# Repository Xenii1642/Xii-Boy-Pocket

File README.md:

<picture> <source media="(prefers-color-scheme: dark)" srcset="Images/XBP-Logo-Light.png" width="800">  </picture> 

The Xii-Boy Pocket is a small portable Wii using a Game Boy form factor. The Xii-Boy Pocket is the second version of my Xii-Boy design.
This new portable Wii is now better, thinner, and above all, Open-Source ! Compared to the Gboy Rev III, it is 25% smaller and 5mm thinner !

If you want to learn more about it, you can check this BitBuilt Thread: [Xii-Boy Pocket's Thread](https://bitbuilt.net/forums/index.php?threads/the-xii-boy-pocket-v2.6638/)

If you want to see its development, you can check this BitBuilt Worklog: [Xii-Boy Pocket's Worklog](https://bitbuilt.net/forums/index.php?threads/xii-boy-v2-xeniis-second-portable-wii.6374/)

You can also learn more about the Xii-Boy Original here: [Xii-Boy Original Thread](https://bitbuilt.net/forums/index.php?threads/the-xii-boy-xeniis-first-portable-wii.6327/)

If you have any questions or problems about the Xii-Boy Pocket, please let me know 😉 Enjoy !

# Parts
All the parts you need to assemble a Xii-Boy Pocket are listed in the [Xii-Boy V2 Parts List.pdf](https://github.com/Xenii1642/Xii-Boy-Pocket/blob/main/Xii-Boy%20V2%20Parts%20List.pdf) file.

⚠ NOTE ⚠ For the batteries, I personally order mine through [Akkuteile](https://akkuteile.de/). However, if you don't live in Europe, you should buy your batteries somewhere else.
You just have to order two 18650 batteries. You shouldn't order them through Aliexpress, they could be fake and maybe dangerous

# PCB
All the Gerbers you need for the Xii-Boy Pocket are available in the [Gerber](https://github.com/Xenii1642/Xii-Boy-Pocket/tree/main/PCB%20Files/Gerber) folder.

All the needed components are listed in the [Xii-Boy V2 PCB BOM.pdf](https://github.com/Xenii1642/Xii-Boy-Pocket/blob/main/Xii-Boy%20V2%20PCB%20BOM.pdf) file.

The Xii-Boy Pocket's PCBs need specific settings to work properly:

### **Controller PCB**:
- ENIG surface finish 
  
### **Xii-Flex**:
- 0.12mm thickness
- Stiffener Polyimide 0.2 mm
  
### **Main PCB**:
- Impedance Controll YES
- Impedance Controll profile JLC04161H-7628

The other PCBs don't need specific settings. You can just let the setting by default 👍

I personally ordered mine through [JLCPCB](https://jlcpcb.com/) 👍

# Case
All the needed STLs are available in the [STL](https://github.com/Xenii1642/Xii-Boy-Pocket/tree/main/STL) folder.
If you want to order your case in **nylon** or **resin** through [JLC3DP](https://jlc3dp.com/), please use the case available in the [Case (JLC)](https://github.com/Xenii1642/Xii-Boy-Pocket/tree/main/STL/Case%20(JLC)) folder.

Otherwise, if you want to print / order it in FDM, use the case available in the [Case (FDM)](https://github.com/Xenii1642/Xii-Boy-Pocket/tree/main/STL/Case%20(FDM)) folder.

⚠️ Some of the buttons and fixations are too small to be manufactured by JLC3DP. To fix that, you can find a file which contains all the too small pieces [here](https://github.com/Xenii1642/Xii-Boy-Pocket/blob/main/STL/Buttons/Buttons-JLC.stl) ⚠️

I personally ordered my case through [JLC3DP](https://jlc3dp.com/) in **nylon SLS** and I printed the buttons in PLA 👍

⚠ NOTE ⚠ JLC3DP may ask you that there are some risks that the case could have warping or cracks. You have to accept them 👍

# STEP Files
You would like to make an edit on the case? No worries! You can find STEP files of the case in the [STEP folder](https://github.com/Xenii1642/Xii-Boy-Pocket/tree/main/STEP)

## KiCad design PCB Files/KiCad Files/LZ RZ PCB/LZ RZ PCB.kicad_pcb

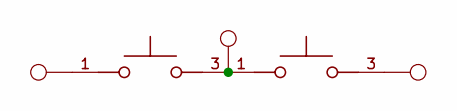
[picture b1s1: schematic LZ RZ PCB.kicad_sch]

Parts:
S1, S2: TL3315NF250Q; SW_TL3315NF250Q
TP1: LZ; TestPoint_Pad_D1.0mm
TP2: GND; TestPoint_Pad_D1.0mm
TP3: RZ; TestPoint_Pad_D1.0mm

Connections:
unnamed: S1.1, TP1.1
unnamed: S1.3, S2.1, TP2.1
unnamed: S2.3, TP3.1

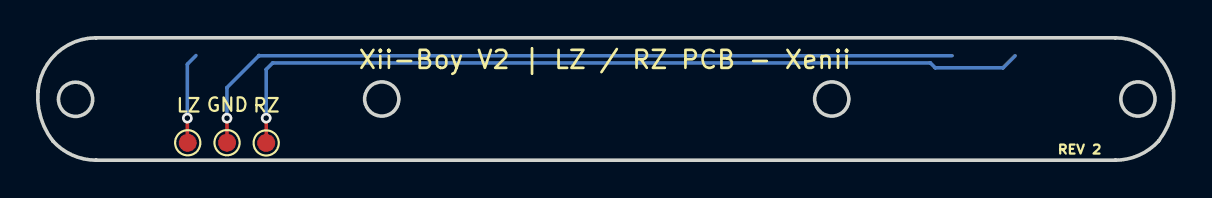
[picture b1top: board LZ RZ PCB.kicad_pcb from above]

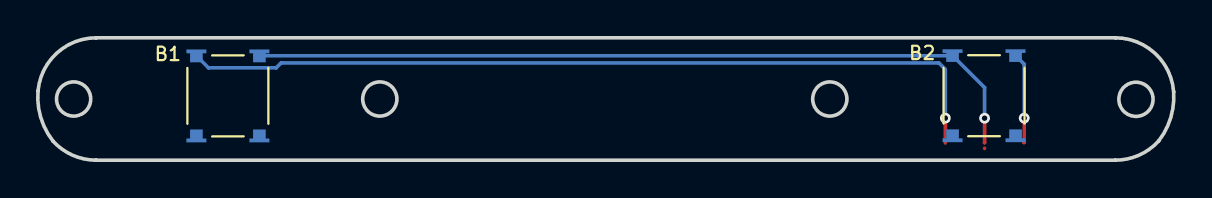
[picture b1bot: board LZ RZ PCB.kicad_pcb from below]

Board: 2 copper layers, 63.1 x 6.8 mm, 5 parts (2 on the bottom side), 3 nets.

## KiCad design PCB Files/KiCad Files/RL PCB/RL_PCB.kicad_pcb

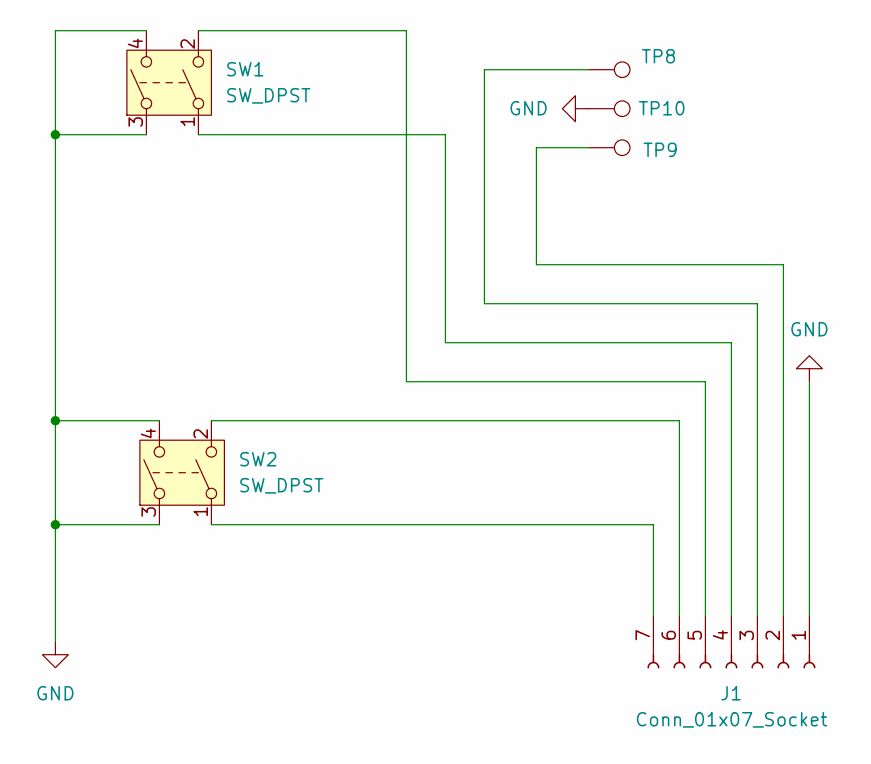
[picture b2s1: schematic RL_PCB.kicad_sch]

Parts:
J1: Conn_01x07_Socket; CON_5051100792_MOL
SW1, SW2: SW_DPST; TMHF07
TP8, TP9, TP10: TestPoint; TestPoint_Pad_D1.0mm

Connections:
GND: J1.1, SW1.3, SW1.4, SW2.3, SW2.4, TP10.1
unnamed: J1.2, TP9.1
unnamed: J1.3, TP8.1
unnamed: J1.4, SW1.1
unnamed: J1.5, SW1.2
unnamed: J1.6, SW2.2
unnamed: J1.7, SW2.1

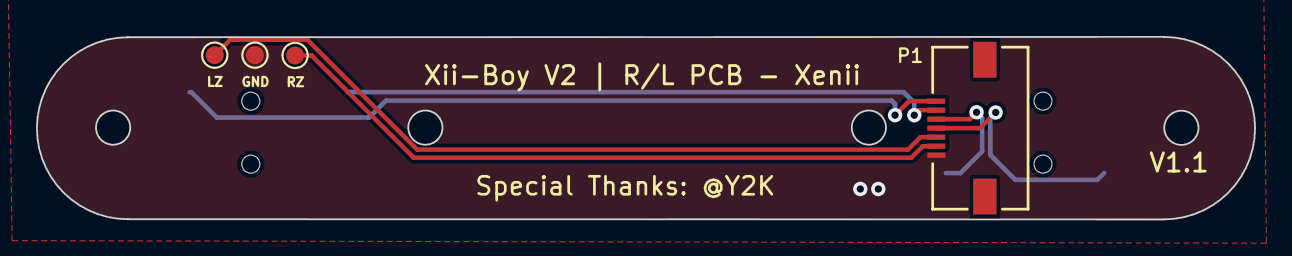
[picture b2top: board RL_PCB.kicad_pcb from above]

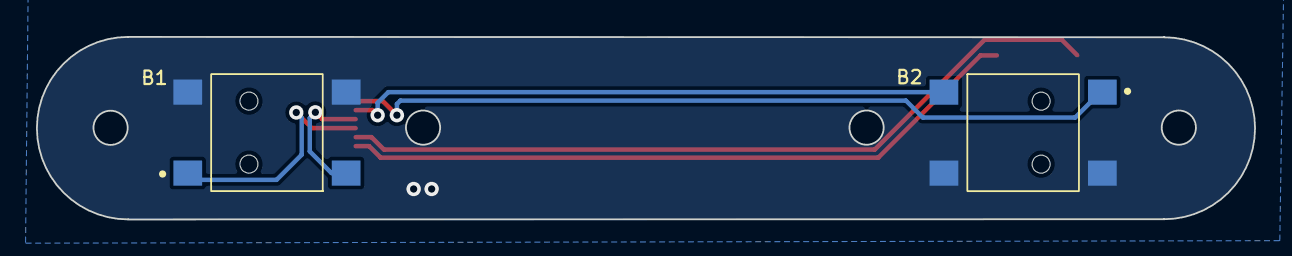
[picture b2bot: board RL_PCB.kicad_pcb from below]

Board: 2 copper layers, 67.7 x 10.1 mm, 6 parts (2 on the bottom side), 7 nets.

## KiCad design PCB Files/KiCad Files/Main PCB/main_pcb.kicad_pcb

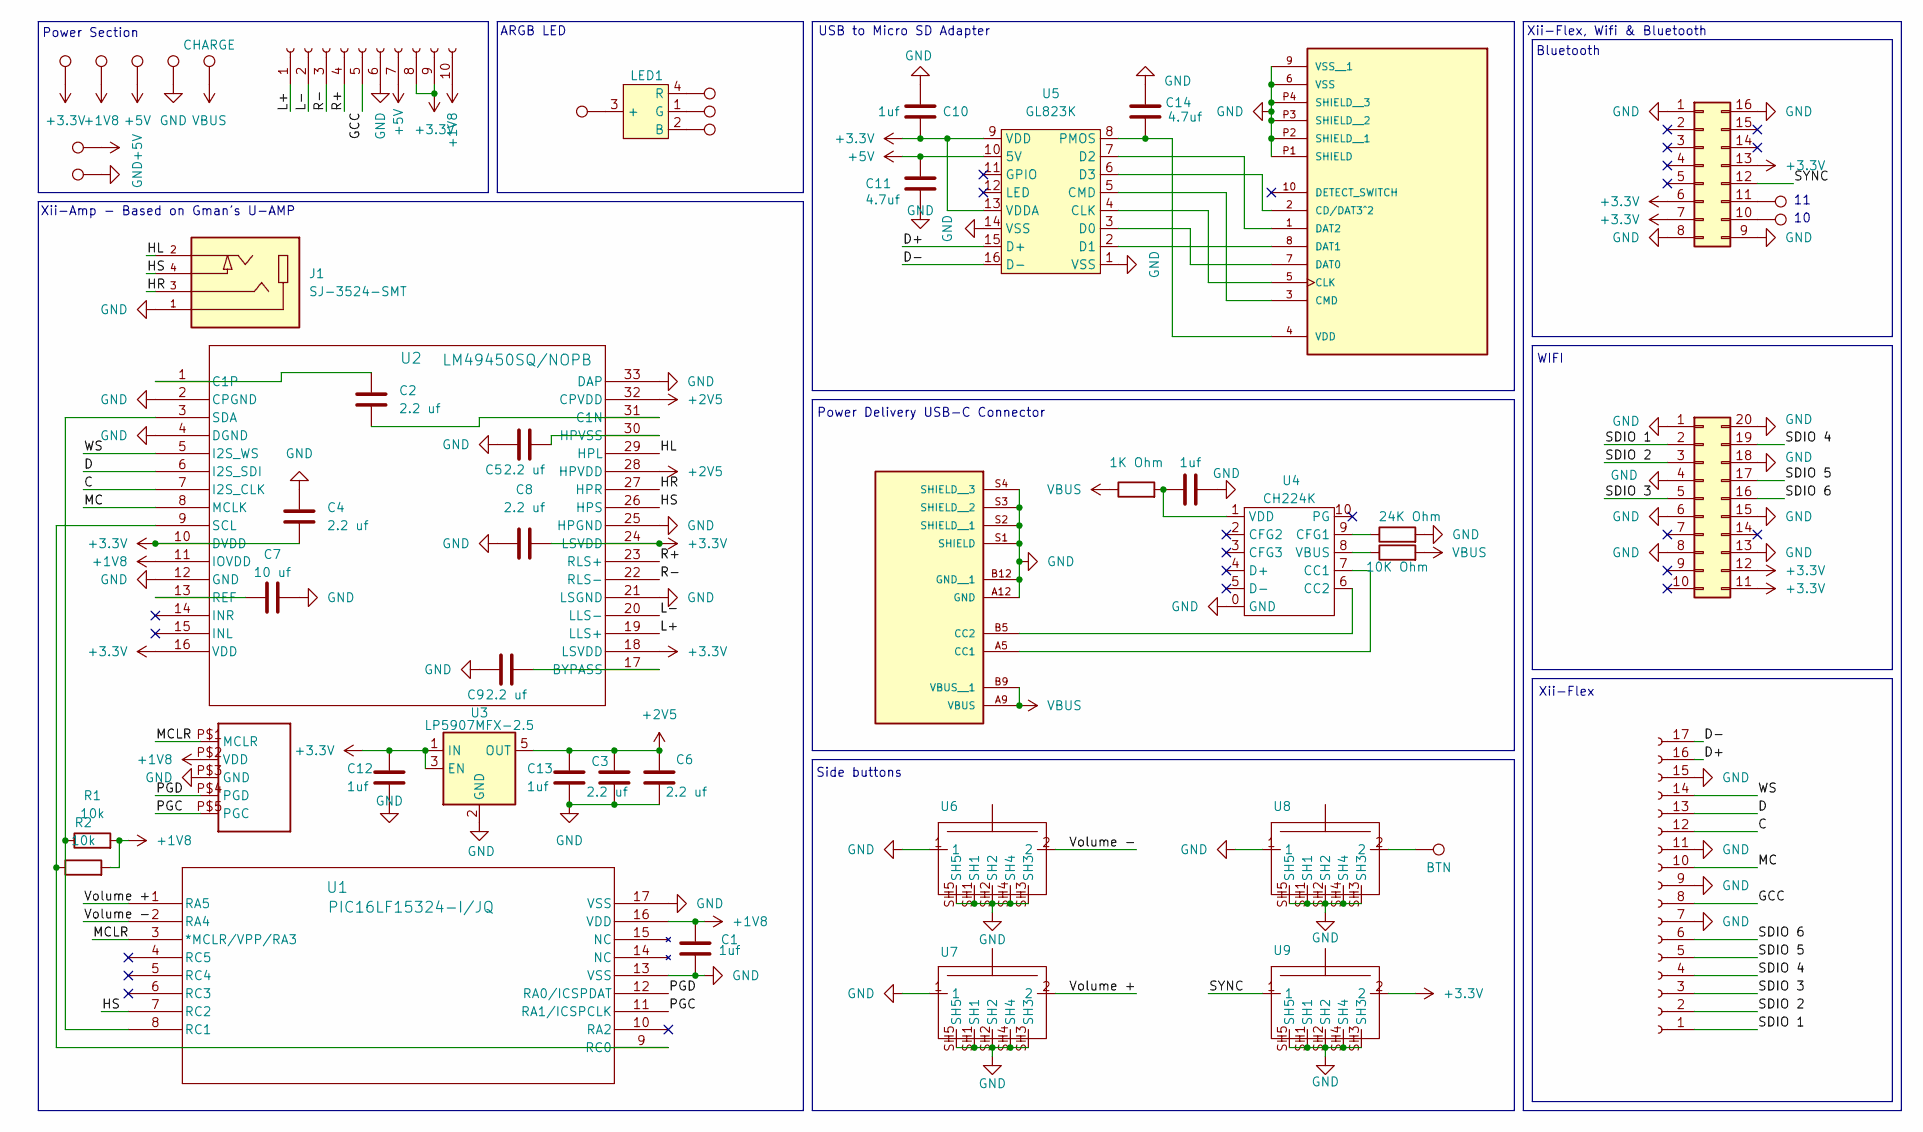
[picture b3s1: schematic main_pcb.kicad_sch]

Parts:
C1, C10, C12, C13, C15: 1uf; C_0402_1005Metric
C2, C3, C4, C5, C6, C8, C9: 2.2 uf; C_0402_1005Metric
C7: 10 uf; C_0402_1005Metric
C11, C14: 4.7uf; C_0402_1005Metric
J1: SJ-3524-SMT; CUI_SJ-3524-SMT; PARTREV 1.03
J2: USB4125-GF-A_REVA2; GCT_USB4125-GF-A_REVA2; PARTREV Rev A2
J3: 503398-1892; MOLEX_503398-1892; PARTREV 0
J4: Conn_01x10_Socket; CON_5051101092_MOL
J5: Conn_01x17_Socket; CON_5051101792_MOL
J6: Conn_02x08_Counter_Clockwise; CON_541020164
J7: Conn_02x10_Counter_Clockwise; CON_529910208
LED1: LED_B38G3RGB-10D0003H2U1930
PH1: GC+2_PROGRAMMING_HEADER; programmer
R1, R2: 10k; R_0402_1005Metric
R3: 1K Ohm; R_0402_1005Metric
R4: 24K Ohm; R_0402_1005Metric
R5: 10K Ohm; R_0402_1005Metric
TP1, TP2, TP3, TP6, TP7, TP8: TestPoint; Xenii-Voltage-Pad
TP4, TP5, TP10, TP11, TP12, TP13: TestPoint; TestPoint_Pad_D1.0mm
TP9: CHARGE; Xenii-Voltage-Pad
TP14: BTN; TestPoint_Pad_D1.0mm
U1: PIC16LF15324-I/JQ; U-Amp_pic
U2: LM49450SQ/NOPB; U-Amp LM49450SQ
U3: LP5907MFX-2.5; SOT-23-5
U4: CH224K; ESSOP-10
U5: GL823K; SSOP-16_3.9x4.9mm_P0.635mm
U6, U7, U8, U9: SW_TL3336AF160Q

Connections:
+1V8: C1.1, J4.10, PH1.P$2 (VDD), R1.2, R2.2, TP2.1, U1.16 (VDD), U2.11 (IOVDD)
+2V5: C3.2, C6.2, C13.1, U2.28 (HPVDD), U2.32 (CPVDD), U3.5 (OUT)
+3.3V: C4.2, C8.2, C10.2, C12.1, J4.8, J4.9, J6.6, J6.7, J6.13, J7.11, J7.12, TP1.1, U2.10 (DVDD), U2.16 (VDD), U2.18 (LSVDD), U2.24 (LSVDD), U3.1 (IN), U3.3 (EN), U5.9 (VDD), U5.13 (VDDA), U9.2
+5V: C11.1, J4.7, TP3.1, TP6.1, U5.10 (5V)
/C: J5.12, U2.7 (I2S_CLK)
/D: J5.13, U2.6 (I2S_SDI)
/D+: J5.16, U5.15 (D+)
/D-: J5.17, U5.16 (D-)
/GCC: J4.5, J5.8
/HL: J1.2, U2.29 (HPL)
/HR: J1.3, U2.27 (HPR)
/HS: J1.4, U1.7 (RC2), U2.26 (HPS)
/L+: J4.1, U2.19 (LLS+)
/L-: J4.2, U2.20 (LLS-)
/MC: J5.10, U2.8 (MCLK)
/MCLR: PH1.P$1 (MCLR), U1.3 (*MCLR/VPP/RA3)
/PGC: PH1.P$5 (PGC), U1.11 (RA1/ICSPCLK)
/PGD: PH1.P$4 (PGD), U1.12 (RA0/ICSPDAT)
/R+: J4.4, U2.23 (RLS+)
/R-: J4.3, U2.22 (RLS-)
/SDIO 1: J5.1, J7.2
/SDIO 2: J5.2, J7.3
/SDIO 3: J5.3, J7.5
/SDIO 4: J5.4, J7.19
/SDIO 5: J5.5, J7.17
/SDIO 6: J5.6, J7.16
/SYNC: J6.12, U9.1
/Volume +: U1.1 (RA5), U7.2
/Volume -: U1.2 (RA4), U6.2
/WS: J5.14, U2.5 (I2S_WS)
GND: C1.2, C3.1, C4.1, C5.1, C6.1, C7.2, C8.1, C9.1, C10.1, C11.2, C12.2, C13.2, C14.2, C15.2, J1.1, J2.A12 (GND), J2.B12 (GND__1), J2.S1 (SHIELD), J2.S2 (SHIELD__1), J2.S3 (SHIELD__2), J2.S4 (SHIELD__3), J3.6 (VSS), J3.9 (VSS__1), J3.P1 (SHIELD), J3.P2 (SHIELD__1), J3.P3 (SHIELD__2), J3.P4 (SHIELD__3), J4.6, J5.7, J5.9, J5.11, J5.15, J6.1, J6.8, J6.9, J6.16, J7.1, J7.4, J7.6, J7.8, J7.13, J7.15, J7.18, J7.20, PH1.P$3 (GND), R4.2, TP7.1, TP8.1, U1.13 (VSS), U1.17 (VSS), U2.2 (CPGND), U2.4 (DGND), U2.12 (GND), U2.21 (LSGND), U2.25 (HPGND), U2.33 (DAP), U3.2 (GND), U4.0 (GND), U5.1 (VSS), U5.14 (VSS), U6.1, U6.SH1, U6.SH2, U6.SH3, U6.SH4, U6.SH5, U7.1, U7.SH1, U7.SH2, U7.SH3, U7.SH4, U7.SH5, U8.1, U8.SH1, U8.SH2, U8.SH3, U8.SH4, U8.SH5, U9.SH1, U9.SH2, U9.SH3, U9.SH4, U9.SH5
unnamed: J2.A5 (CC1), U4.7 (CC1)
unnamed: J2.B5 (CC2), U4.6 (CC2)
unnamed: J3.2 (CD/DAT3^2), U5.6 (D3)
unnamed: J3.5 (CLK), U5.4 (CLK)
unnamed: J3.3 (CMD), U5.5 (CMD)
unnamed: J3.7 (DAT0), U5.3 (D0)
unnamed: J3.8 (DAT1), U5.2 (D1)
unnamed: J3.1 (DAT2), U5.7 (D2)
unnamed: C14.1, J3.4 (VDD), U5.8 (PMOS)
unnamed: J6.10, TP5.1
unnamed: J6.11, TP4.1
unnamed: LED1.3 (+), TP10.1
unnamed: LED1.2 (B), TP13.1
unnamed: LED1.1 (G), TP12.1
unnamed: LED1.4 (R), TP11.1
unnamed: TP14.1, U8.2
unnamed: R2.1, U1.9 (RC0), U2.9 (SCL)
unnamed: R1.1, U1.8 (RC1), U2.3 (SDA)
unnamed: C9.2, U2.17 (BYPASS)
unnamed: C2.2, U2.31 (C1N)
unnamed: C2.1, U2.1 (C1P)
unnamed: C5.2, U2.30 (HPVSS)
unnamed: C7.1, U2.13 (REF)
unnamed: R4.1, U4.9 (CFG1)
unnamed: R5.1, U4.8 (VBUS)
unnamed: C15.1, R3.2, U4.1 (VDD)
VBUS: J2.A9 (VBUS), J2.B9 (VBUS__1), R3.1, R5.2, TP9.1

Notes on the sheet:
Xii-Amp - Based on Gman's U-AMP
Xii-Flex
Xii-Flex, Wifi & Bluetooth
Power Section
WIFI
Bluetooth
Side buttons
ARGB LED
Power Delivery USB-C Connector
USB to Micro SD Adapter

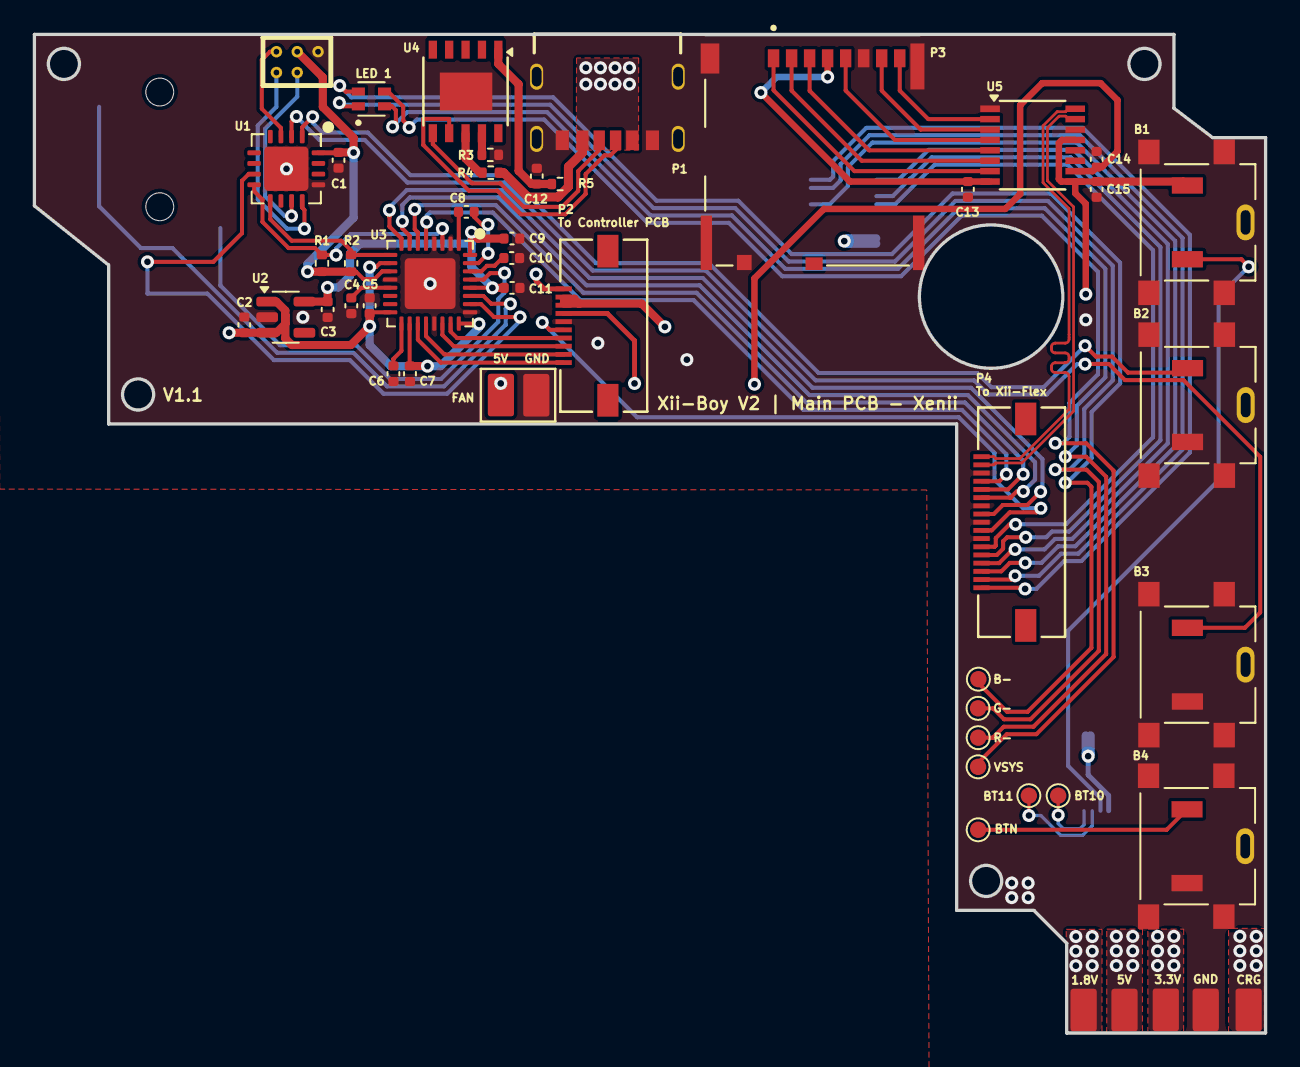
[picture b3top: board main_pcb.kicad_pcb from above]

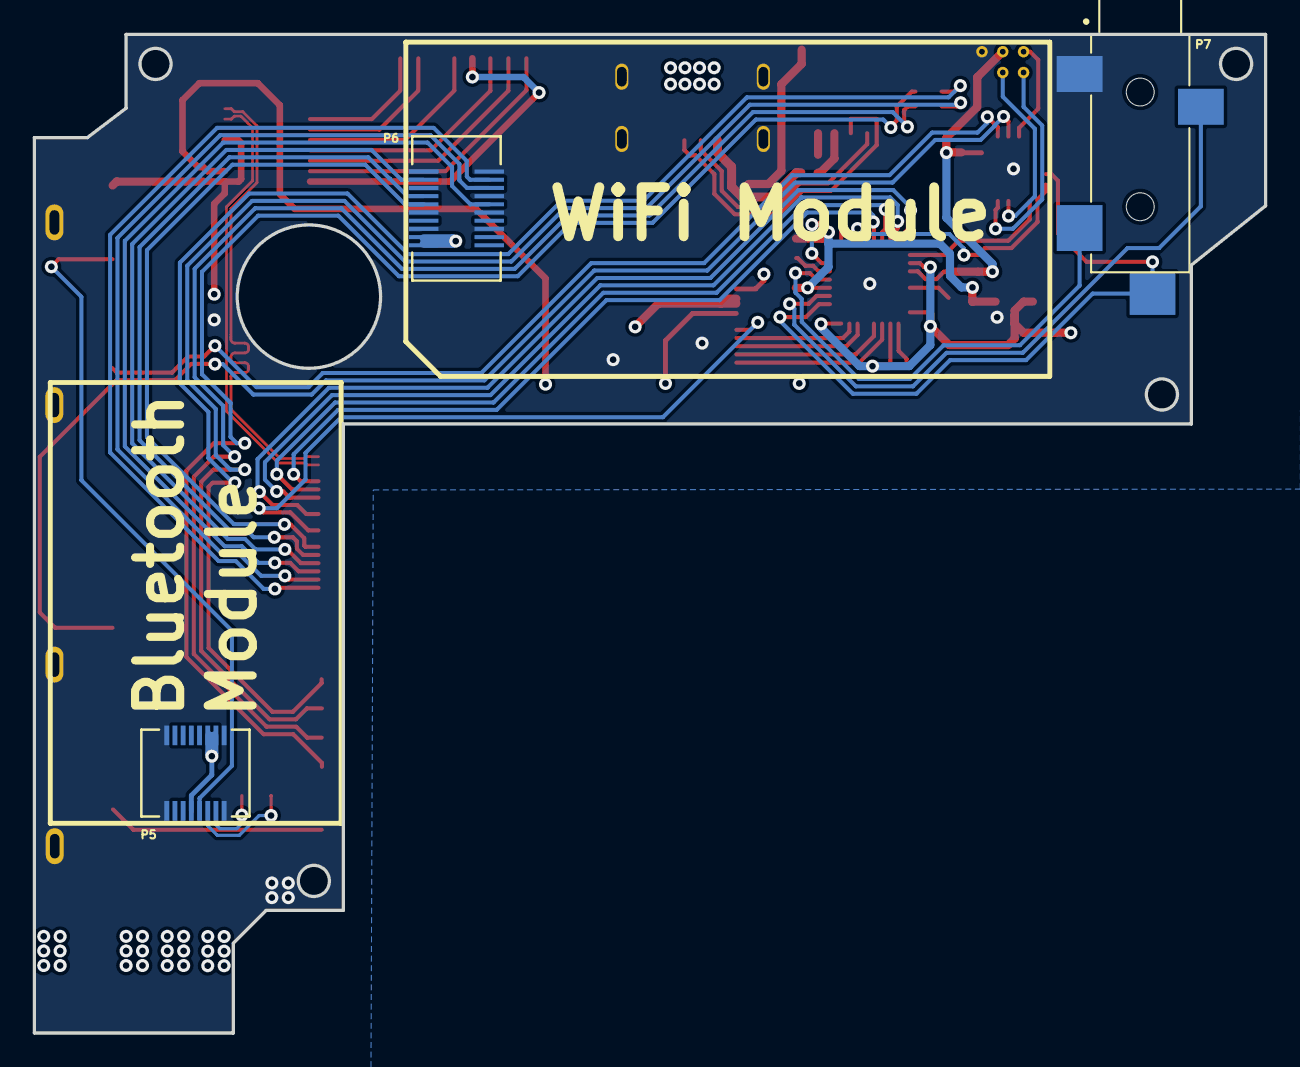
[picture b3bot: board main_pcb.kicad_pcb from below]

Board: 4 copper layers, 75.1 x 60.9 mm, 52 parts (3 on the bottom side), 58 nets.

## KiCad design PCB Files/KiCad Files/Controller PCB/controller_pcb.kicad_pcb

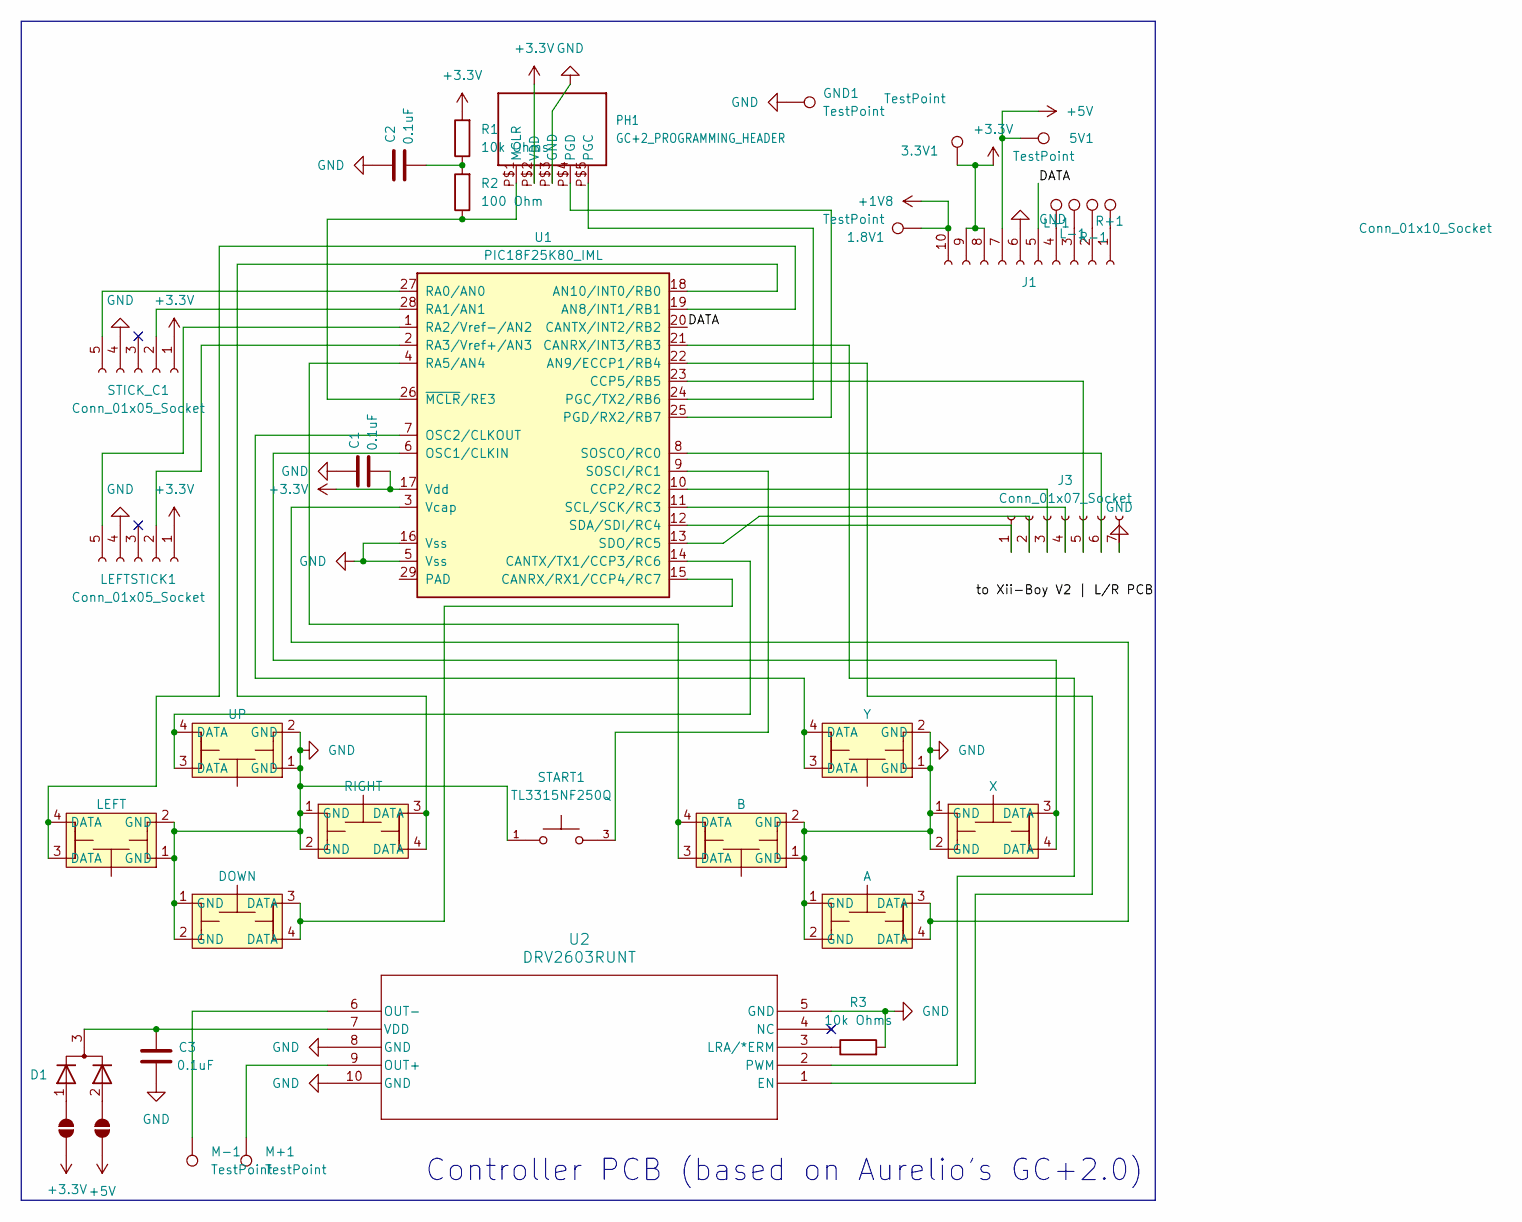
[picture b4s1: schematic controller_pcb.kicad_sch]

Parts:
1.8V1, 3.3V1, 5V1: TestPoint; TestPoint_Pad_D1.0mm
C1, C2, C3: 0.1uF; C_0402_1005Metric
D1: D_Dual_CommonCathode_AAK_Parallel; SOT_05CT215_NEX-L
DSL_Pad1: LEFT; DSL_Pad
DSL_Pad2: UP; DSL_Pad
DSL_Pad3: DOWN; DSL_Pad
DSL_Pad4: RIGHT; DSL_Pad
DSL_Pad5: B; DSL_Pad
DSL_Pad6: Y; DSL_Pad
DSL_Pad7: A; DSL_Pad
DSL_Pad8: X; DSL_Pad
GND1: TestPoint; TestPoint_Pad_D1.0mm
J1: Conn_01x10_Socket; CON_5051101092_MOL
J3: Conn_01x07_Socket; CON_5051100792_MOL
JP1, JP2: SolderJumper_2_Open; SolderJumper-2_P1.3mm_Open_RoundedPad1.0x1.5mm
L+1: TestPoint; TestPoint_Pad_D1.0mm
L-1: TestPoint; TestPoint_Pad_D1.0mm
LEFTSTICK1: Conn_01x05_Socket; CON_5051100592_MOL
M+1: TestPoint; TestPoint_Pad_D1.0mm
M-1: TestPoint; TestPoint_Pad_D1.0mm
PH1: GC+2_PROGRAMMING_HEADER; programmer
R1, R3: 10k Ohms; R_0402_1005Metric
R2: 100 Ohm; R_0402_1005Metric
R+1: TestPoint; TestPoint_Pad_D1.0mm
R-1: TestPoint; TestPoint_Pad_D1.0mm
START1: TL3315NF250Q; SW_TL3315NF250Q
STICK_C1: Conn_01x05_Socket; CON_5051100592_MOL
U1: PIC18F25K80_IML; PIC18F2542 (GC+ 2.0)
U2: DRV2603RUNT; RUN10_TEX

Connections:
+1V8: 1.8V1.1, J1.10
+3.3V: 3.3V1.1, C1.1, J1.8, J1.9, JP1.1 (A), LEFTSTICK1.1, PH1.P$2 (VDD), R1.2, STICK_C1.1, U1.17 (Vdd)
+5V: 5V1.1, J1.7, JP2.2 (B)
/DATA: J1.5, U1.20 (CANTX/INT2/RB2)
GND: C1.2, C2.2, C3.1, DSL_Pad1.1 (GND), DSL_Pad1.2 (GND), DSL_Pad2.1 (GND), DSL_Pad2.2 (GND), DSL_Pad3.1 (GND), DSL_Pad3.2 (GND), DSL_Pad4.1 (GND), DSL_Pad4.2 (GND), DSL_Pad5.1 (GND), DSL_Pad5.2 (GND), DSL_Pad6.1 (GND), DSL_Pad6.2 (GND), DSL_Pad7.1 (GND), DSL_Pad7.2 (GND), DSL_Pad8.1 (GND), DSL_Pad8.2 (GND), GND1.1, J1.6, J3.7, LEFTSTICK1.4, PH1.P$3 (GND), R3.2, START1.1, STICK_C1.4, U1.5 (Vss), U1.16 (Vss), U1.PAD, U2.5 (GND), U2.8 (GND), U2.10 (GND)
unnamed: C2.1, R1.1, R2.2
unnamed: C3.2, D1.3 (A), U2.7 (VDD)
unnamed: J1.1, R+1.1
unnamed: J1.2, R-1.1
unnamed: J1.3, L-1.1
unnamed: J1.4, L+1.1
unnamed: J3.1, U1.12 (SDA/SDI/RC4)
unnamed: J3.2, U1.13 (SDO/RC5)
unnamed: J3.3, U1.10 (CCP2/RC2)
unnamed: J3.4, U1.11 (SCL/SCK/RC3)
unnamed: J3.5, U1.23 (CCP5/RB5)
unnamed: J3.6, U1.8 (SOSCO/RC0)
unnamed: D1.1 (K), JP1.2 (B)
unnamed: D1.2 (K), JP2.1 (A)
unnamed: LEFTSTICK1.2, U1.2 (RA3/Vref+/AN3)
unnamed: LEFTSTICK1.5, U1.1 (RA2/Vref-/AN2)
unnamed: PH1.P$1 (MCLR), R2.1, U1.26 (~MCLR/RE3)
unnamed: PH1.P$5 (PGC), U1.24 (PGC/TX2/RB6)
unnamed: PH1.P$4 (PGD), U1.25 (PGD/RX2/RB7)
unnamed: STICK_C1.2, U1.28 (RA1/AN1)
unnamed: STICK_C1.5, U1.27 (RA0/AN0)
unnamed: DSL_Pad1.3 (DATA), DSL_Pad1.4 (DATA), U1.19 (AN8/INT1/RB1)
unnamed: U1.22 (AN9/ECCP1/RB4), U2.1 (EN)
unnamed: DSL_Pad4.3 (DATA), DSL_Pad4.4 (DATA), U1.18 (AN10/INT0/RB0)
unnamed: U1.21 (CANRX/INT3/RB3), U2.2 (PWM)
unnamed: DSL_Pad3.3 (DATA), DSL_Pad3.4 (DATA), U1.15 (CANRX/RX1/CCP4/RC7)
unnamed: DSL_Pad2.3 (DATA), DSL_Pad2.4 (DATA), U1.14 (CANTX/TX1/CCP3/RC6)
unnamed: DSL_Pad8.3 (DATA), DSL_Pad8.4 (DATA), U1.6 (OSC1/CLKIN)
unnamed: DSL_Pad6.3 (DATA), DSL_Pad6.4 (DATA), U1.7 (OSC2/CLKOUT)
unnamed: DSL_Pad5.3 (DATA), DSL_Pad5.4 (DATA), U1.4 (RA5/AN4)
unnamed: START1.3, U1.9 (SOSCI/RC1)
unnamed: DSL_Pad7.3 (DATA), DSL_Pad7.4 (DATA), U1.3 (Vcap)
unnamed: R3.1, U2.3 (LRA/*ERM)
unnamed: M+1.1, U2.9 (OUT+)
unnamed: M-1.1, U2.6 (OUT-)

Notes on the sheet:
Controller PCB (based on Aurelio's GC+2.0)

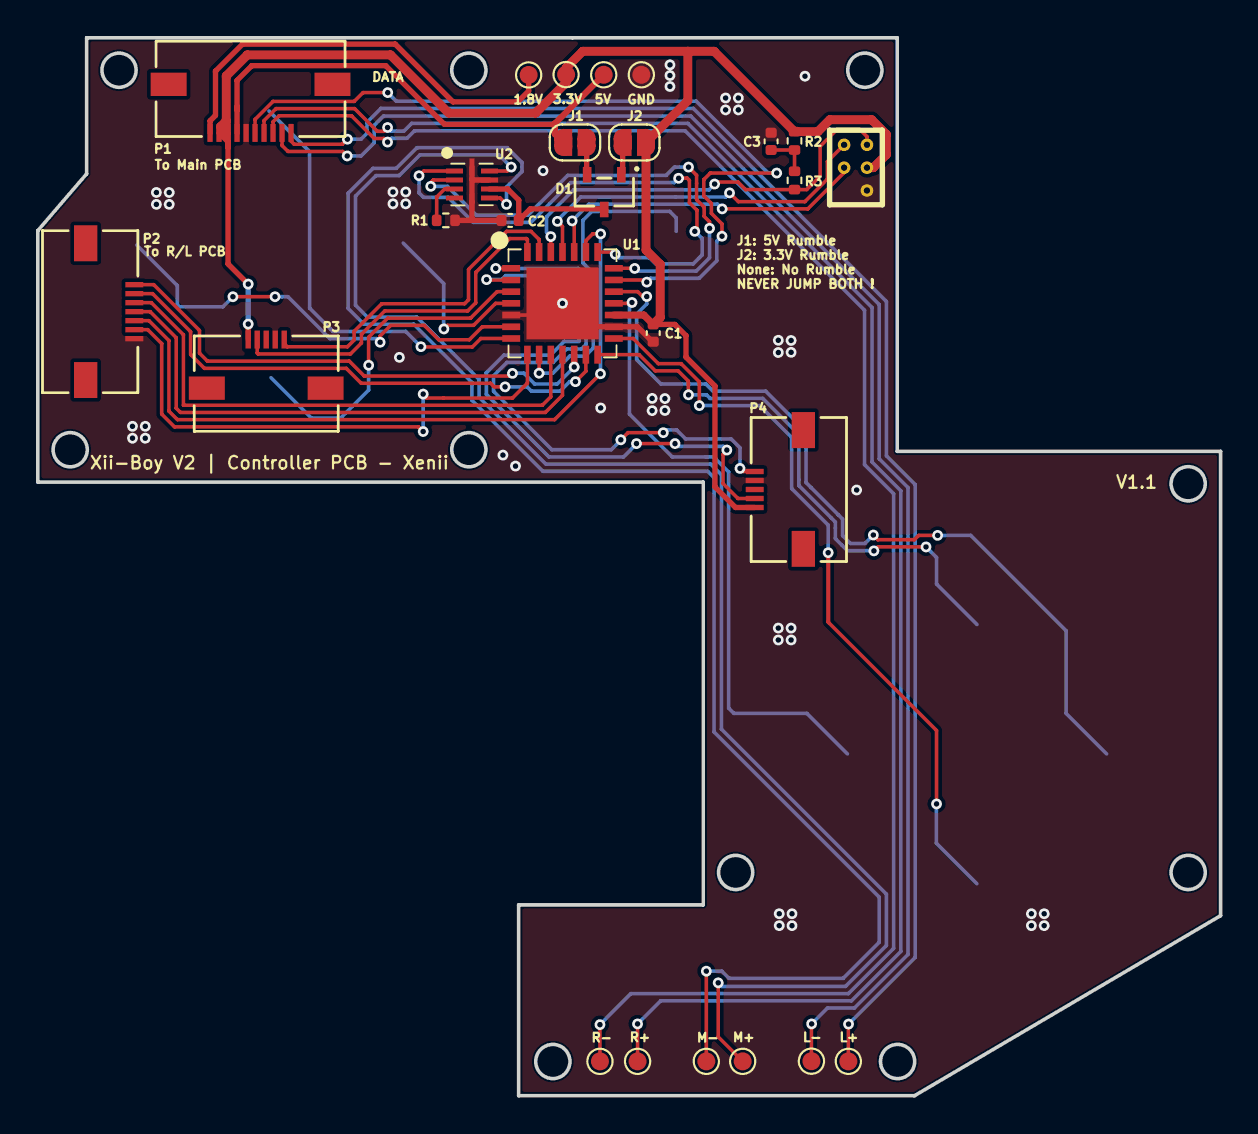
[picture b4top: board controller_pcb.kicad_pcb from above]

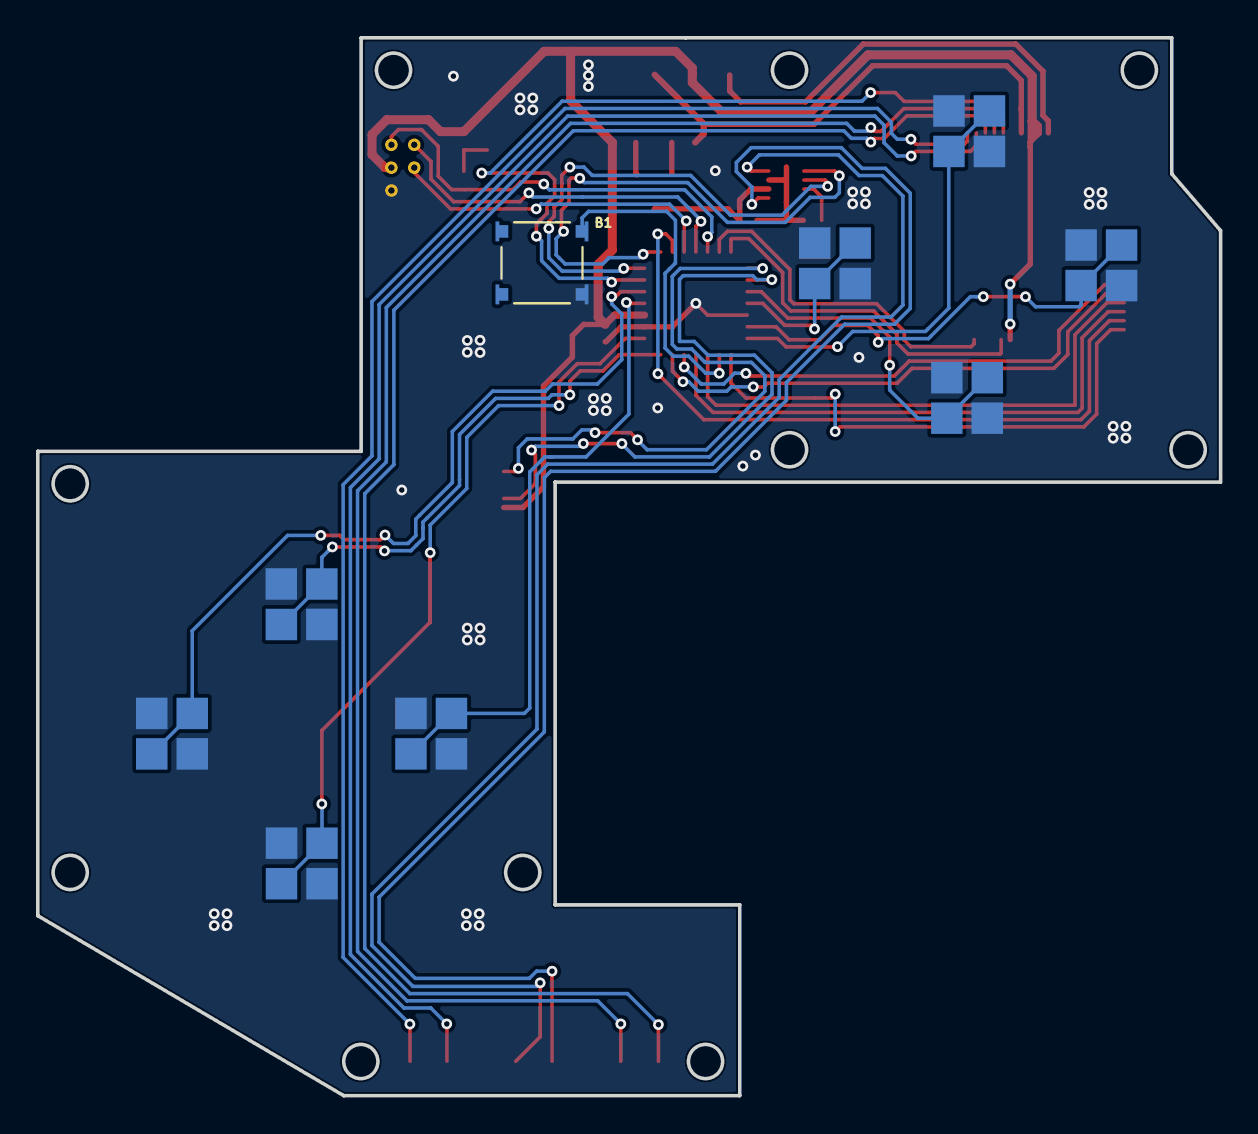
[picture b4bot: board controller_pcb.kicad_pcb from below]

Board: 2 copper layers, 65.7 x 58.8 mm, 35 parts (9 on the bottom side), 40 nets.

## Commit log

2024-10-31 README.md
2025-01-19 revision of Xii-Flex for JLC
    The Wi-Fi SDIO vias have moved to make the Xii-Flex compatible with JLC.
2025-01-19 New top case revision
    Upgrade the screen fitment.
2025-01-19 Button group for JLC
    This file contains all the too small buttons and group them.
2025-01-19 Add Xii-Boy Pocket Stand (compatible with XiiSBar)
2025-01-30 Add STEP files for limitless case edits!
